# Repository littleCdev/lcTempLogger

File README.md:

# lcTempLogger
lcTemplogger is a simple ESP8266 temperature-logger using the DS18B22 onewire sensors to feed iot-databases like emoncms / thinkspeak / etc.
You can flash the software onto the ESP8266 without editing the code, setting up the wifi is done via a webinterface.

## Sleep mode
the used ESP8266-01 requires the GPIO 16 wired to RST to wake up from deepsleep mode. if you don't do this the ESP will 
never wake up on itself.

## Powersaving
To not drain the batteries too much, the ESP will shutdown after 5 minutes of inactivity in configuration mode, you can simply wake it up again by pressing the reset button.

I suggest to remove the red power-led from the board. This can be done using a soldering iron or just break it out carefully.

## Building
Building and flashing is done via the Arduino-IDE

add the ESP to your IDE following this guide 
https://github.com/esp8266/Arduino#installing-with-boards-manager

All other required libraries like onewire and the DS18B22 are included into the sketch. Go to arduino/lcTempLogger/ and open lcTempLogger.ino and hit the uploadbutton

Settings
* Board "Generic ESP8266 Module"
* Flash Mode "DIO"
* Flash Frequency "40MHz"
* CPU Frequency "80MHz"
* Flash Size "1M (512k SPIFFS)"
* Debug port "Disabled"
* Debug Level "None"
* Reset Method "ck"
* Upload Speed "115200"

#### uploading the sketchdata
Use the [esp8266fs-plugin](https://github.com/esp8266/arduino-esp8266fs-plugin) to upload the data into the spiffs.

After including the plugin into the IDE you can simply hit tool->ESP8266 Sketch Data Upload 

## Configuring
If done everything correctly you should be able to find a wifi called "LC-ESP8266-XXXXXXXX",
 connect to it with the password "12345678" (yes, i know it is insecure, but the wifi will be on for configuration only) 
and open 192.168.1.4 in a webbrowser. Select your Network, enter the password and hit "Save" after waiting a bit 
(the ESP is sometimes slow with connecting) until the Wifistatus changes to "connected".

#### API's
Under "API's" you are able to select a preset for emoncms or thinkspeak, just replace your apikey with the placesholder.
I you want to use another API just add the URL, the method (Post or Get) and set the headers and Postdata.
Hit save and try making a testcall under "Test API", you will see the response in the textbox below the testbutton.

If everything works go to the top of the page and hit "Start" to set the ESP to deepsleep.

#### Aborting deepsleep
if you want to wake up the ESP to change settings like API, wifi or whatever press the reset-button, after that you have 2 seconds 
to press the "Set" button once and the ESP will wake up with the accesspoint enabled for configuring. (You need to start the deepsleep again via the webinterface)

## Boards
the board is designed to work with normal AAA-batteries or a 3.7V Lipo including a simple charging circuit using the TP4056 and a MCP1700 as voltageregulator.
You can find the eagle-files in eagle/ (eagle version 7.5)
Boards can be easily ordered at [aisler.net](https://aisler.net/littleCdev/my-project-repository/esp8266-templogger)

Example boards from aisler, left: AAA-battery powered, right using a 3.7V 500mAh lipo battery with charger

>For AAA-battery powered boards set SJ1 and **don't** place following components 
* IC1 
* IC3
* R1
* R2
* R3
* D1
* D2

# Licence MIT
Copyright 2017 Matthias Böck

Permission is hereby granted, free of charge, to any person obtaining a copy of this software and associated documentation files (the "Software"), to deal in the Software without restriction, including without limitation the rights to use, copy, modify, merge, publish, distribute, sublicense, and/or sell copies of the Software, and to permit persons to whom the Software is furnished to do so, subject to the following conditions:

The above copyright notice and this permission notice shall be included in all copies or substantial portions of the Software.

THE SOFTWARE IS PROVIDED "AS IS", WITHOUT WARRANTY OF ANY KIND, EXPRESS OR IMPLIED, INCLUDING BUT NOT LIMITED TO THE WARRANTIES OF MERCHANTABILITY, FITNESS FOR A PARTICULAR PURPOSE AND NONINFRINGEMENT. IN NO EVENT SHALL THE AUTHORS OR COPYRIGHT HOLDERS BE LIABLE FOR ANY CLAIM, DAMAGES OR OTHER LIABILITY, WHETHER IN AN ACTION OF CONTRACT, TORT OR OTHERWISE, ARISING FROM, OUT OF OR IN CONNECTION WITH THE SOFTWARE OR THE USE OR OTHER DEALINGS IN THE SOFTWARE.

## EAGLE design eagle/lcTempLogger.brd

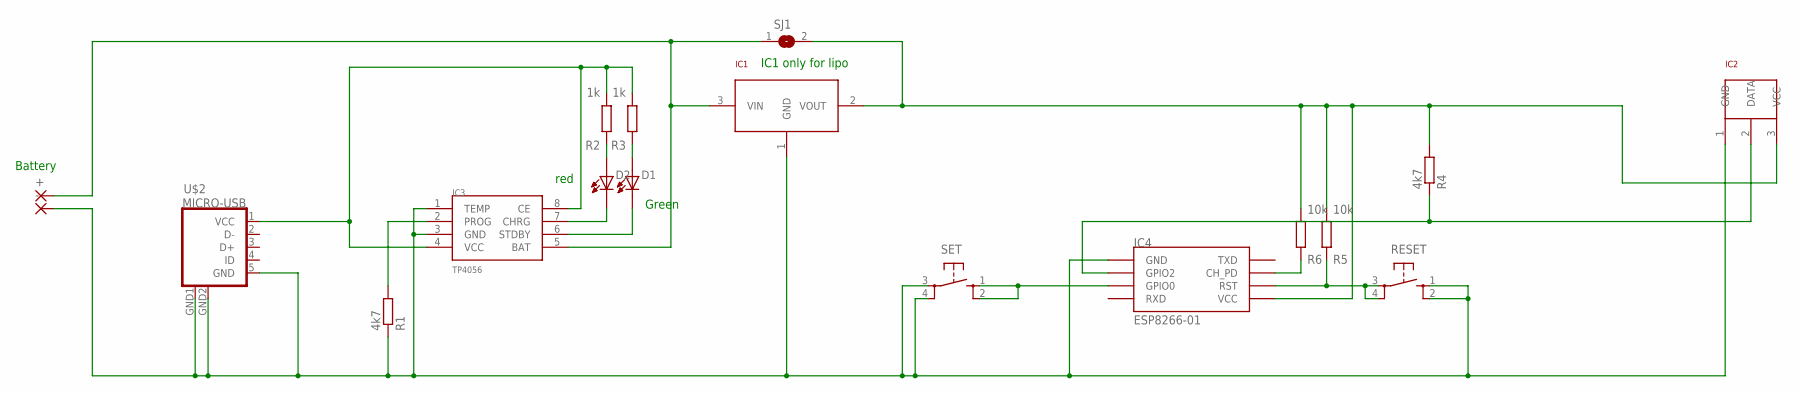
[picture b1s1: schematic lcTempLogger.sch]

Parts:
+: 1,6/0,8
-: 1,6/0,8
D1, D2: LED-0805; CHIPLED_0805
IC1: MCP1700; SOT-23
IC2: DS18B20TO-92; TO-92
IC3: TP4056; SOP-8
IC4: ESP8266-01; ESP01
R1, R4: 4k7; R1206
R2, R3: 1k; R0805
R5, R6: 10k; R1206
RESET: 10-XX; B3F-10XX
SET: 10-XX; B3F-10XX
SJ1: SJ
U$2: MICRO-USB

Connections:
3V: IC1.2 (VOUT), IC2.3 (VCC), IC4.VCC, R4.2, R5.2, R6.2, SJ1.2
5V_USB: IC3.4 (VCC), IC3.8 (CE), R2.2, R3.2, U$2.1 (VCC)
GND: -.1, IC1.1 (GND), IC2.1 (GND), IC3.1 (TEMP), IC3.3 (GND), IC4.GND, R1.1, RESET.1, RESET.2, SET.3, SET.4, U$2.5 (GND), U$2.GND1 (GND), U$2.GND2 (GND)
unnamed: D2.C (K), IC3.7 (CHRG)
unnamed: IC2.2 (DATA), IC4.GPIO2, R4.1
unnamed: +.1, IC1.3 (VIN), IC3.5 (BAT), SJ1.1
unnamed: IC4.GPIO0, SET.1, SET.2
unnamed: D1.C (K), IC3.6 (STDBY)
unnamed: IC3.2 (PROG), R1.2
unnamed: D2.A, R2.1
unnamed: D1.A, R3.1
unnamed: IC4.RST, R5.1, RESET.3, RESET.4
unnamed: IC4.CH_PD, R6.1

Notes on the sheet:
Battery
IC1 only for lipo
Green
red

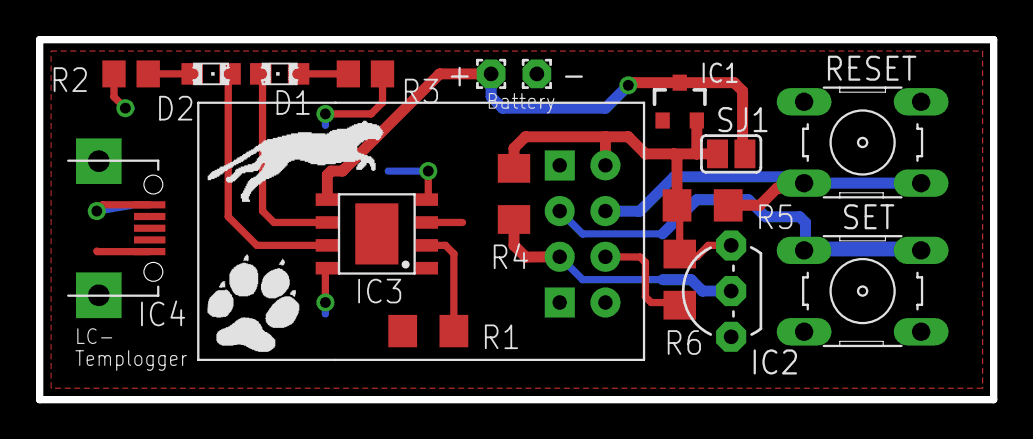
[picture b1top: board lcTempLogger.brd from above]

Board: 2 copper layers, 53.0 x 20.0 mm, 20 parts (0 on the bottom side), 13 nets.

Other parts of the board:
U$1: LOGO-21-SMALL-PAW
U$3: LOGO-21-MIDDLE-CHEETAH

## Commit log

2017-12-29 markupfix
2017-12-29 added aisler project and picture of the boards
2018-03-02 removed comment, sleep even longer
2018-03-02 do not start as AP if you want to conenct to a wifi
